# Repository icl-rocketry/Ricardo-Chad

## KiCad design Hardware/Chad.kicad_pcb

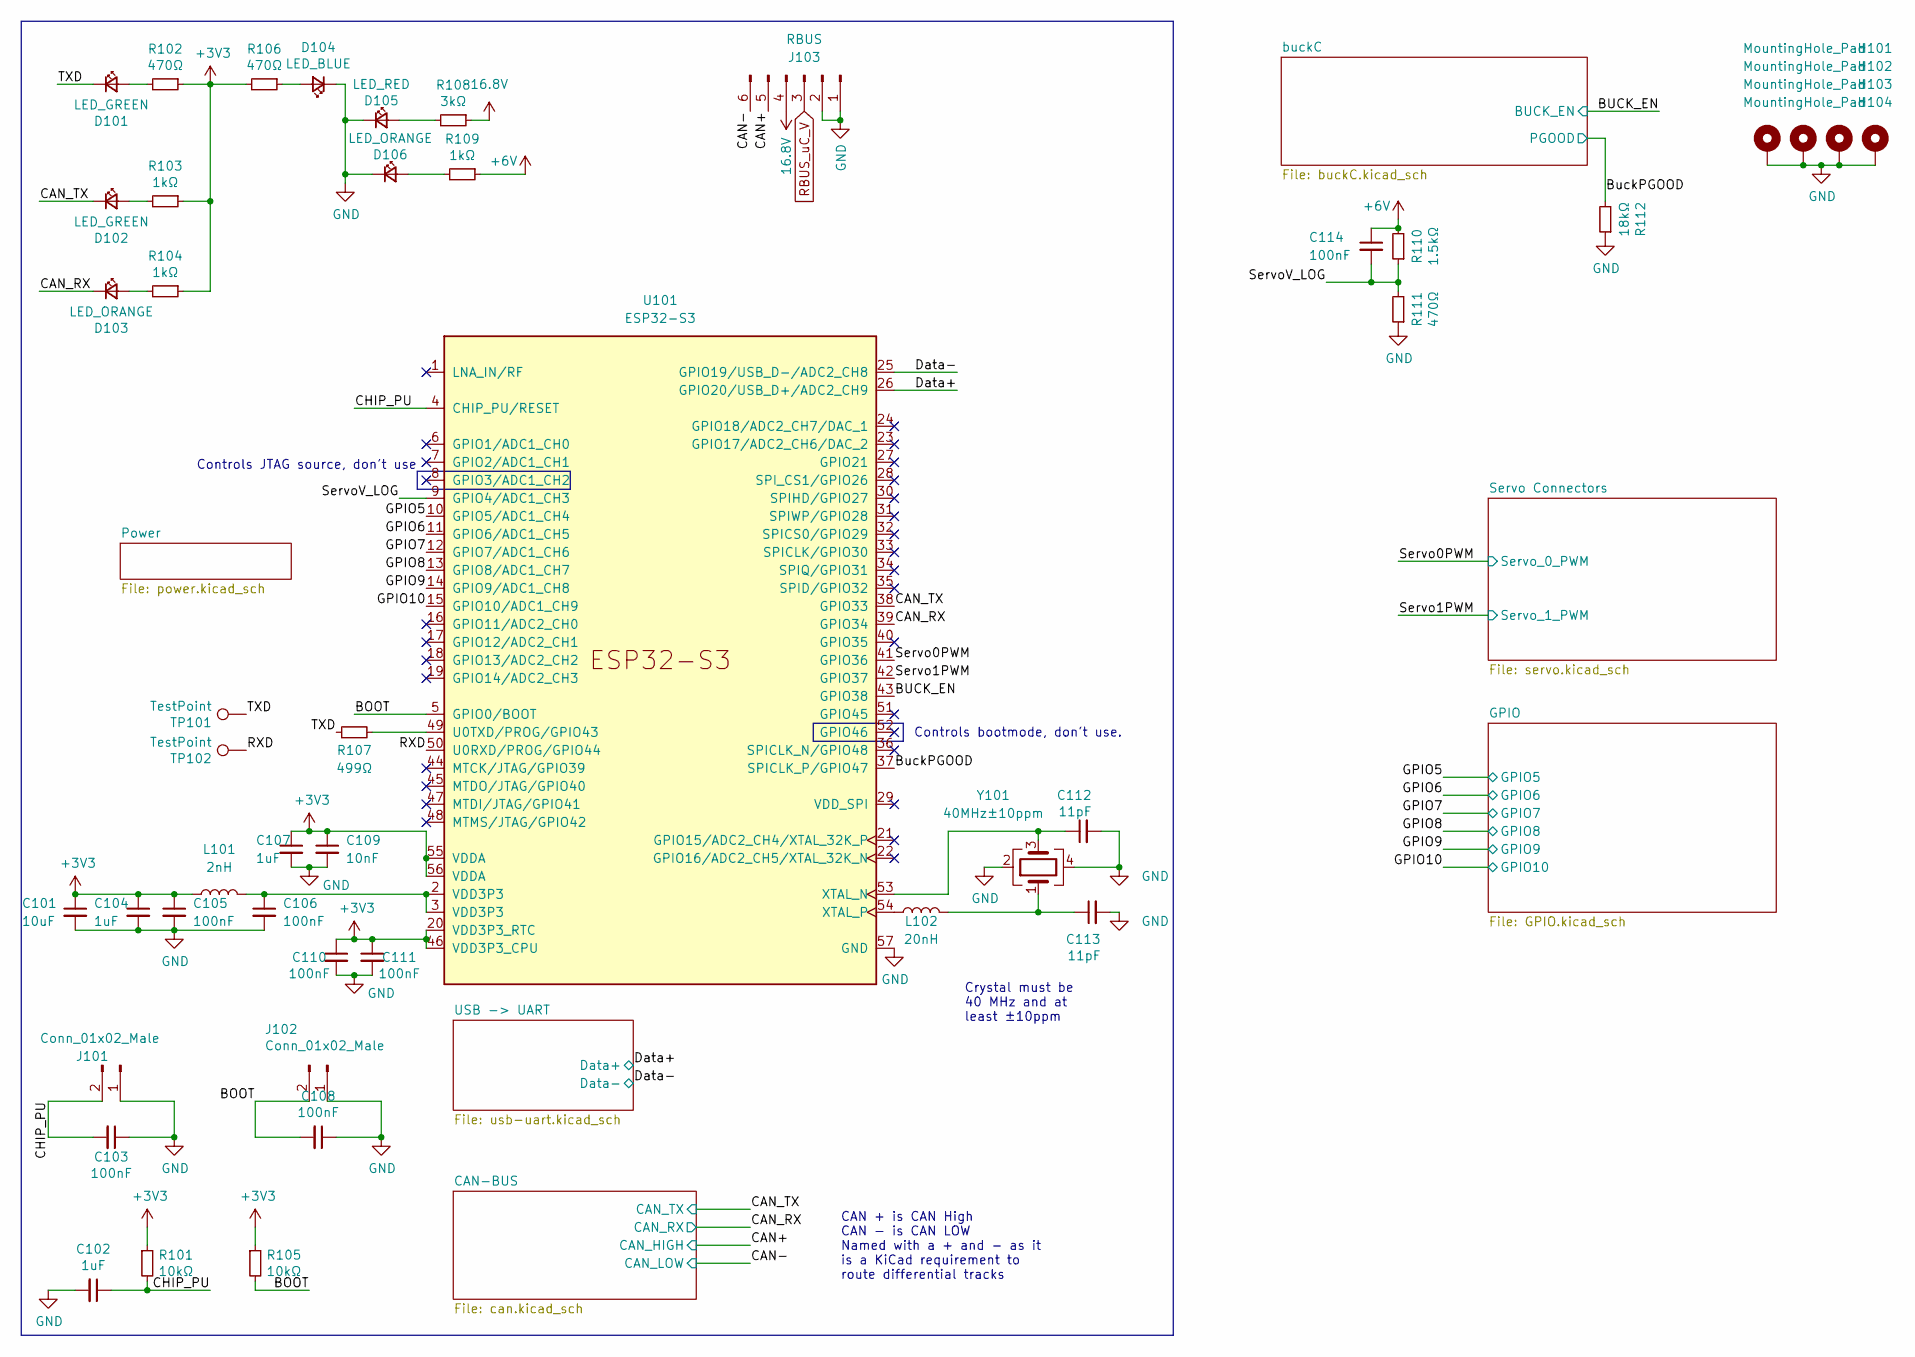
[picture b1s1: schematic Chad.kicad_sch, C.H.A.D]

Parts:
C101: 10uF; C_0402_1005Metric
C102, C104, C107: 1uF; C_0402_1005Metric
C103, C105, C106, C108, C110, C111, C114: 100nF; C_0402_1005Metric
C109: 10nF; C_0402_1005Metric
C112, C113: 11pF; C_0402_1005Metric
D101, D102: LED_GREEN; LED_0402_1005Metric
D103, D106: LED_ORANGE; LED_0402_1005Metric
D104: LED_BLUE; LED_0402_1005Metric
D105: LED_RED; LED_0402_1005Metric
H101, H102, H103, H104: MountingHole_Pad; MountingHole_3.2mm_M3_DIN965_Pad
J101, J102: Conn_01x02_Male; PinHeader_1x02_P2.54mm_Vertical
J103: RBUS; Molex_Mini-Fit_Jr_5569-06A2_2x03_P4.20mm_Horizontal
L101: 2nH; L_0402_1005Metric
L102: 20nH; L_0402_1005Metric
R101, R105: 10kΩ; R_0402_1005Metric
R102, R106, R111: 470Ω; R_0402_1005Metric
R103, R104, R109: 1kΩ; R_0402_1005Metric
R107: 499Ω; R_0402_1005Metric; MPN AC0402FR-07499RL
R108: 3kΩ; R_0402_1005Metric
R110: 1.5kΩ; R_0402_1005Metric
R112: 18kΩ; R_0402_1005Metric
TP101, TP102: TestPoint; TestPoint_Pad_D1.0mm
U101: ESP32-S3; QFN40P700X700X90-57N
Y101: 40MHz±10ppm; Crystal_SMD_2016-4Pin_2.0x1.6mm; MPN R940000171

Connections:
+3V3: C101.1, C104.1, C105.1, C107.1, C109.1, C110.1, C111.1, L101.1, R101.1, R102.1, R103.1, R104.1, R105.1, R106.2, U101.20 (VDD3P3_RTC), U101.46 (VDD3P3_CPU), U101.55 (VDDA), U101.56 (VDDA); also elsewhere on the board
+6V: C114.1, R109.1, R110.2; also elsewhere on the board
+16.8V: J103.4, R108.1; also elsewhere on the board
/BOOT: C108.2, J102.2, R105.2, U101.5 (GPIO0/BOOT)
/BUCK_EN: U101.43 (GPIO38); also elsewhere on the board
/BuckPGOOD: R112.2, U101.37 (SPICLK_P/GPIO47); also elsewhere on the board
/CAN+: J103.5; also elsewhere on the board
/CAN-: J103.6; also elsewhere on the board
/CAN_RX: D103.1 (K), U101.39 (GPIO34); also elsewhere on the board
/CAN_TX: D102.1 (K), U101.38 (GPIO33); also elsewhere on the board
/CHIP_PU: C102.1, C103.2, J101.2, R101.2, U101.4 (CHIP_PU/RESET)
/Data+: U101.26 (GPIO20/USB_D+/ADC2_CH9); also elsewhere on the board
/Data-: U101.25 (GPIO19/USB_D-/ADC2_CH8); also elsewhere on the board
/GPIO5: U101.10 (GPIO5/ADC1_CH4); also elsewhere on the board
/GPIO6: U101.11 (GPIO6/ADC1_CH5); also elsewhere on the board
/GPIO7: U101.12 (GPIO7/ADC1_CH6); also elsewhere on the board
/GPIO8: U101.13 (GPIO8/ADC1_CH7); also elsewhere on the board
/GPIO9: U101.14 (GPIO9/ADC1_CH8); also elsewhere on the board
/GPIO10: U101.15 (GPIO10/ADC1_CH9); also elsewhere on the board
/RXD: TP102.1, U101.50 (U0RXD/PROG/GPIO44)
/Servo0PWM: U101.41 (GPIO36); also elsewhere on the board
/Servo1PWM: U101.42 (GPIO37); also elsewhere on the board
/ServoV_LOG: C114.2, R110.1, R111.2, U101.9 (GPIO4/ADC1_CH3)
/TXD: D101.1 (K), R107.1, TP101.1
GND: C101.2, C102.2, C103.1, C104.2, C105.2, C106.2, C107.2, C108.1, C109.2, C110.2, C111.2, C112.2, C113.2, D104.1 (K), D105.1 (K), D106.1 (K), H101.1, H102.1, H103.1, H104.1, J101.1, J102.1, J103.1, J103.2, R111.1, R112.1, U101.57 (GND), Y101.2, Y101.4; also elsewhere on the board
unnamed: C106.1, L101.2, U101.2 (VDD3P3), U101.3 (VDD3P3)
unnamed: C113.1, L102.2, Y101.1
unnamed: D101.2 (A), R102.2
unnamed: D102.2 (A), R103.2
unnamed: D103.2 (A), R104.2
unnamed: D104.2 (A), R106.1
unnamed: D105.2 (A), R108.2
unnamed: D106.2 (A), R109.2
unnamed: R107.2, U101.49 (U0TXD/PROG/GPIO43)
unnamed: C112.1, U101.53 (XTAL_N), Y101.3
unnamed: L102.1, U101.54 (XTAL_P)
RBUS_uC_V: J103.3; also elsewhere on the board

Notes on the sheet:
Controls bootmode, don't use.
CAN + is CAN High CAN - is CAN LOW Named with a + and - as it is a KiCad requirement to route differential tracks
Controls JTAG source, don't use
Crystal must be 40 MHz and at least ±10ppm

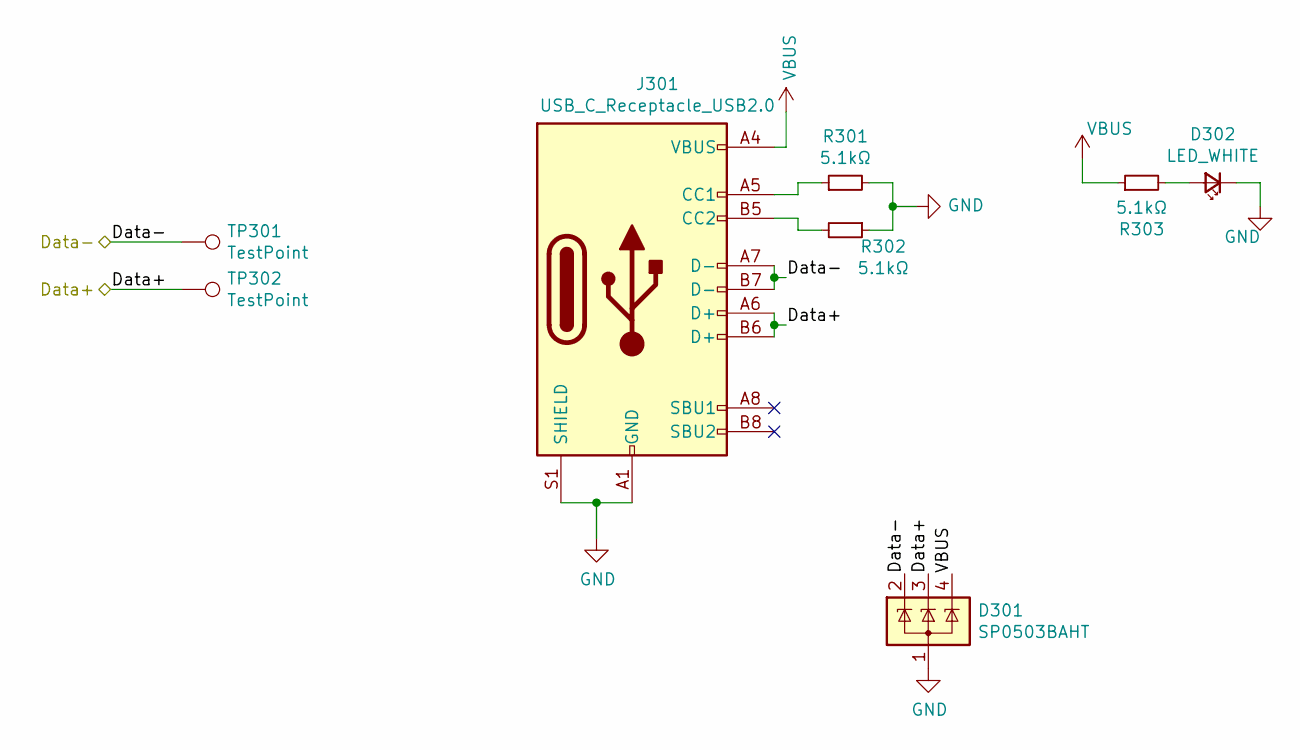
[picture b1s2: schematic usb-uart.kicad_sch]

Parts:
D301: SP0503BAHT; SOT-143
D302: LED_WHITE; LED_0402_1005Metric
J301: USB_C_Receptacle_USB2.0; USB_C_Receptacle_Palconn_UTC16-G
R301, R302, R303: 5.1kΩ; R_0402_1005Metric
TP301, TP302: TestPoint; TestPoint_Pad_D1.0mm

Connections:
/Data+: D301.3 (K), J301.A6 (D+), J301.B6 (D+), TP302.1; also elsewhere on the board
/Data-: D301.2 (K), J301.A7 (D-), J301.B7 (D-), TP301.1; also elsewhere on the board
GND: D301.1 (A), D302.1 (K), J301.A1 (GND), J301.A12 (GND), J301.B1 (GND), J301.B12 (GND), J301.S1 (SHIELD), R301.2, R302.1; also elsewhere on the board
unnamed: D302.2 (A), R303.2
unnamed: J301.A5 (CC1), R301.1
unnamed: J301.B5 (CC2), R302.2
VBUS: D301.4 (K), J301.A4 (VBUS), J301.A9 (VBUS), J301.B4 (VBUS), J301.B9 (VBUS), R303.1; also elsewhere on the board

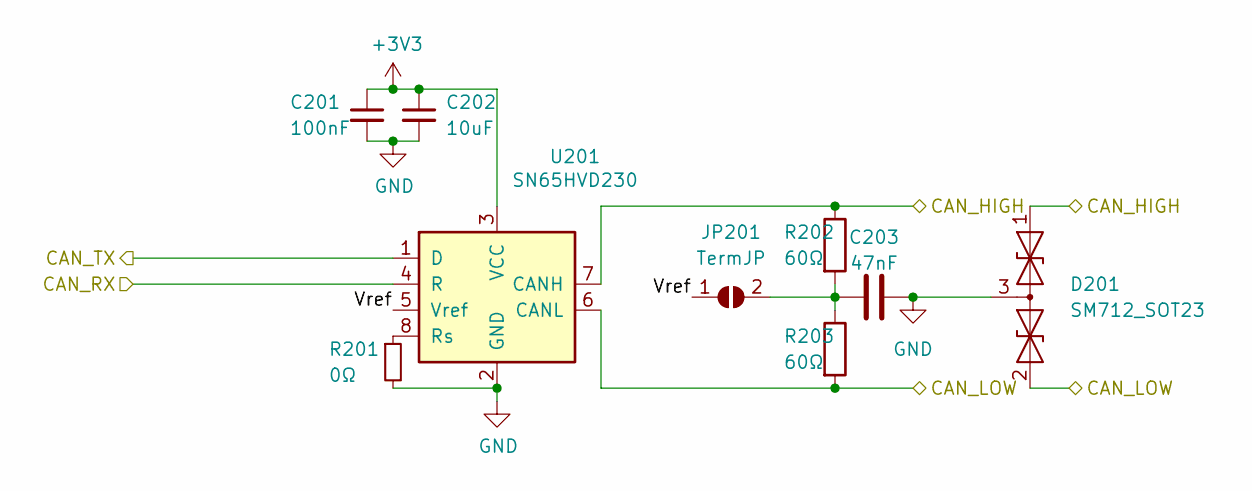
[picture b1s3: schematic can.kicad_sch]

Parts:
C201: 100nF; C_0402_1005Metric
C202: 10uF; C_0402_1005Metric
C203: 47nF; C_0402_1005Metric
D201: SM712_SOT23; SOT-23
JP201: TermJP; SmallerSolderJP
R201: 0Ω; R_0402_1005Metric
R202, R203: 60Ω; R_0603_1608Metric
U201: SN65HVD230; SOIC-8_3.9x4.9mm_P1.27mm

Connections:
+3V3: C201.1, C202.1, U201.3 (VCC); also elsewhere on the board
/CAN+: D201.1 (A1), R202.1, U201.7 (CANH); also elsewhere on the board
/CAN-: D201.2 (A2), R203.2, U201.6 (CANL); also elsewhere on the board
/CAN-BUS/Vref: JP201.1 (A), U201.5 (Vref)
/CAN_RX: U201.4 (R); also elsewhere on the board
/CAN_TX: U201.1 (D); also elsewhere on the board
GND: C201.2, C202.2, C203.2, D201.3 (common), R201.2, U201.2 (GND); also elsewhere on the board
unnamed: C203.1, JP201.2 (B), R202.2, R203.1
unnamed: R201.1, U201.8 (Rs)

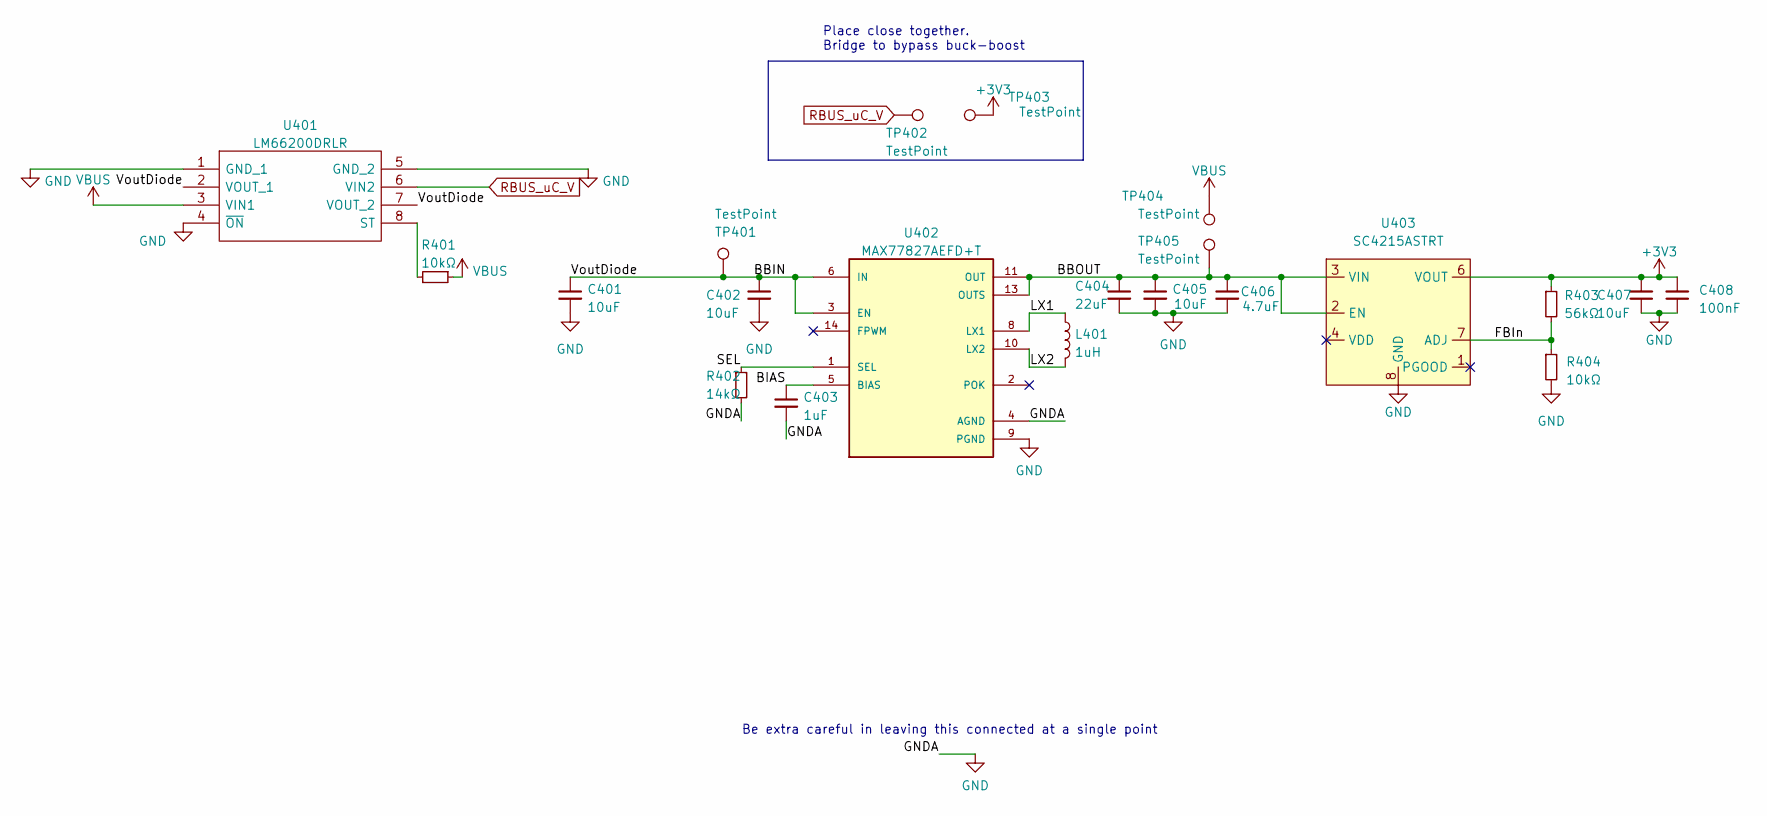
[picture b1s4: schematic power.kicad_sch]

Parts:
C401, C405, C407: 10uF; C_0402_1005Metric
C402: 10uF; C_0603_1608Metric
C403: 1uF; C_0402_1005Metric
C404: 22uF; C_0603_1608Metric
C406: 4.7uF; C_0402_1005Metric
C408: 100nF; C_0402_1005Metric
L401: 1uH; L_0805_2012Metric; MPN DFE201210U-1R0M
R401, R404: 10kΩ; R_0402_1005Metric
R402: 14kΩ; R_0402_1005Metric
R403: 56kΩ; R_0402_1005Metric
TP401, TP402, TP403, TP404, TP405: TestPoint; TestPoint_Pad_D1.5mm
U401: LM66200DRLR; SOTFL50P160X60-8N; Manufacturer_Part_Number LM66200DRLR; Mouser Part Number 595-LM66200DRLR
U402: MAX77827AEFD+T; CONV_MAX77827AEFD+T; PARTREV B
U403: SC4215ASTRT; SOIC127P599X175-9N

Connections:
+3V3: C407.2, C408.2, R403.1, TP403.1, U403.6 (VOUT); also elsewhere on the board
/Power/BBIN: C401.1, C402.1, TP401.1, U401.2 (VOUT_1), U401.7 (VOUT_2), U402.3 (EN), U402.6 (IN)
/Power/BBOUT: C404.1, C405.1, C406.1, TP405.1, U402.11 (OUT), U402.13 (OUTS), U403.2 (EN), U403.3 (VIN)
/Power/BIAS: C403.1, U402.5 (BIAS)
/Power/FBIn: R403.2, R404.1, U403.7 (ADJ)
/Power/LX1: L401.1, U402.8 (LX1)
/Power/LX2: L401.2, U402.10 (LX2)
/Power/SEL: R402.1, U402.1 (SEL)
GND: C401.2, C402.2, C403.2, C404.2, C405.2, C406.2, C407.1, C408.1, R402.2, R404.2, U401.1 (GND_1), U401.4 (~ON), U401.5 (GND_2), U402.4 (AGND), U402.9 (PGND), U403.8 (GND), U403.9 (GND); also elsewhere on the board
unnamed: R401.2, U401.8 (ST)
RBUS_uC_V: TP402.1, U401.6 (VIN2); also elsewhere on the board
VBUS: R401.1, TP404.1, U401.3 (VIN1); also elsewhere on the board

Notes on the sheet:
Place close together. Bridge to bypass buck-boost
Be extra careful in leaving this connected at a single point

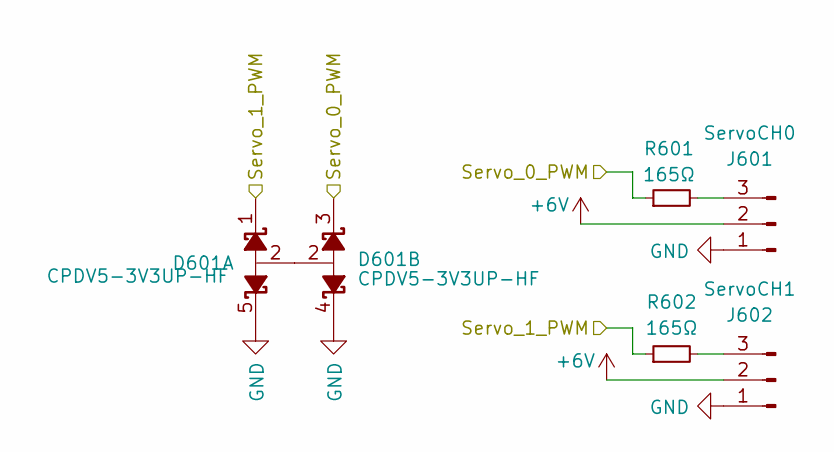
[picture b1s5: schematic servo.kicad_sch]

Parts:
D601: CPDV5-3V3UP-HF; SOT-353_SC-70-5
J601: ServoCH0; Molex_Nano-Fit_105313-xx03_1x03_P2.50mm_Horizontal
J602: ServoCH1; Molex_Nano-Fit_105313-xx03_1x03_P2.50mm_Horizontal
R601, R602: 165Ω; R_0402_1005Metric; MPN RK73H1ETTP1650F

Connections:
+6V: J601.2, J602.2; also elsewhere on the board
/Servo0PWM: D601.3, R601.1; also elsewhere on the board
/Servo1PWM: D601.1, R602.1; also elsewhere on the board
GND: D601.4, D601.5, J601.1, J602.1; also elsewhere on the board
unnamed: J601.3, R601.2
unnamed: J602.3, R602.2

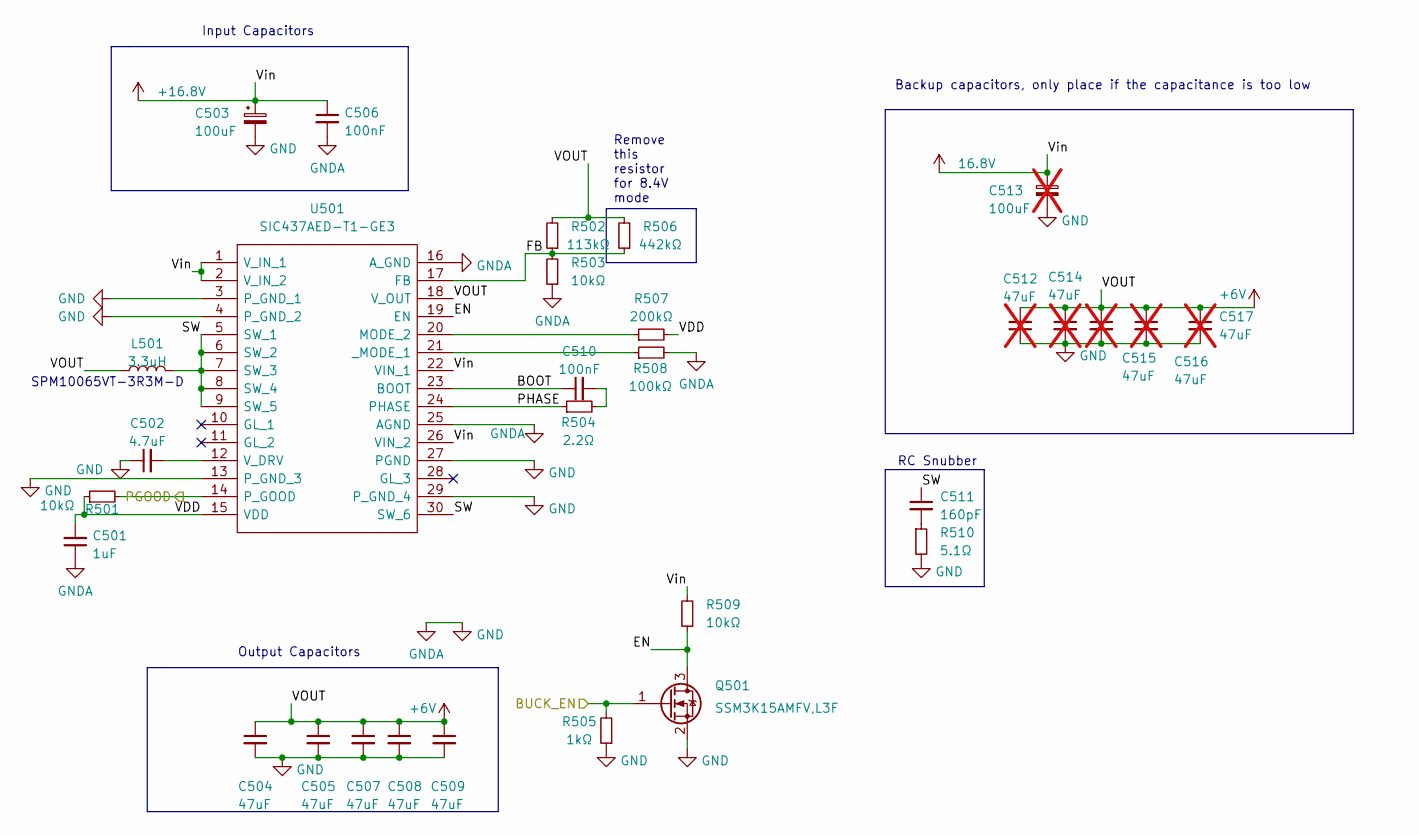
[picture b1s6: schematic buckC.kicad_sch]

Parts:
C501: 1uF; C_0402_1005Metric
C502: 4.7uF; C_0402_1005Metric
C503: 100uF; CP_EIA-7360-38_Kemet-E; MPN T52M1107M035C0100
C504, C505, C507, C508, C509: 47uF; C_1206_3216Metric
C506, C510: 100nF; C_0402_1005Metric
C511: 160pF; C_0603_1608Metric
C512, C514, C515, C516, C517: 47uF; C_1206_3216Metric; not fitted
C513: 100uF; CP_EIA-7360-38_Kemet-E; MPN T52M1107M035C0100; not fitted
L501: 3.3uH; IND_SPM10065VT-3R3M-D; MPN SPM10065VT-3R3M-D
Q501: SSM3K15AMFV,L3F; SOT-723
R501, R503, R509: 10kΩ; R_0402_1005Metric
R502: 113kΩ; R_0402_1005Metric; MPN ERJ-2RKF1133X
R504: 2.2Ω; R_0402_1005Metric
R505: 1kΩ; R_0402_1005Metric
R506: 442kΩ; R_0402_1005Metric; MPN ERJ-2RKF4423X
R507: 200kΩ; R_0402_1005Metric
R508: 100kΩ; R_0402_1005Metric
R510: 5.1Ω; R_0603_1608Metric
U501: SIC437AED-T1-GE3; SiC437BEDT1GE3; Manufacturer_Part_Number SiC437BED-T1-GE3; Mouser Part Number 78-SIC437BED-T1-GE3

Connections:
+6V: C504.1, C505.1, C507.1, C508.1, C509.1, C512.2, C514.1, C515.1, C516.1, C517.1, L501.1, R502.2, R506.2, U501.18 (V_OUT); also elsewhere on the board
+16.8V: C503.1, C506.1, C513.1, R509.2, U501.1 (V_IN_1), U501.2 (V_IN_2), U501.22 (VIN_1), U501.26 (VIN_2); also elsewhere on the board
/BUCK_EN: Q501.1 (G), R505.2; also elsewhere on the board
/BuckPGOOD: R501.2, U501.14 (P_GOOD); also elsewhere on the board
/buckC/BOOT: C510.1, U501.23 (BOOT)
/buckC/EN: Q501.3 (D), R509.1, U501.19 (EN)
/buckC/FB: R502.1, R503.2, R506.1, U501.17 (FB)
/buckC/PHASE: R504.1, U501.24 (PHASE)
/buckC/SW: C511.1, L501.2, U501.5 (SW_1), U501.6 (SW_2), U501.7 (SW_3), U501.8 (SW_4), U501.9 (SW_5), U501.30 (SW_6)
/buckC/VDD: C501.2, R501.1, R507.2, U501.15 (VDD)
GND: C501.1, C502.1, C503.2, C504.2, C505.2, C506.2, C507.2, C508.2, C509.2, C512.1, C513.2, C514.2, C515.2, C516.2, C517.2, Q501.2 (S), R503.1, R505.1, R508.2, R510.2, U501.3 (P_GND_1), U501.4 (P_GND_2), U501.13 (P_GND_3), U501.16 (A_GND), U501.25 (AGND), U501.27 (PGND), U501.29 (P_GND_4); also elsewhere on the board
unnamed: C510.2, R504.2
unnamed: C511.2, R510.1
unnamed: R507.1, U501.20 (MODE_2)
unnamed: C502.2, U501.12 (V_DRV)
unnamed: R508.1, U501.21 (_MODE_1)

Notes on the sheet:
Backup capacitors, only place if the capacitance is too low
RC Snubber
SPM10065VT-3R3M-D
Input Capacitors
Output Capacitors
Remove this resistor for 8.4V mode

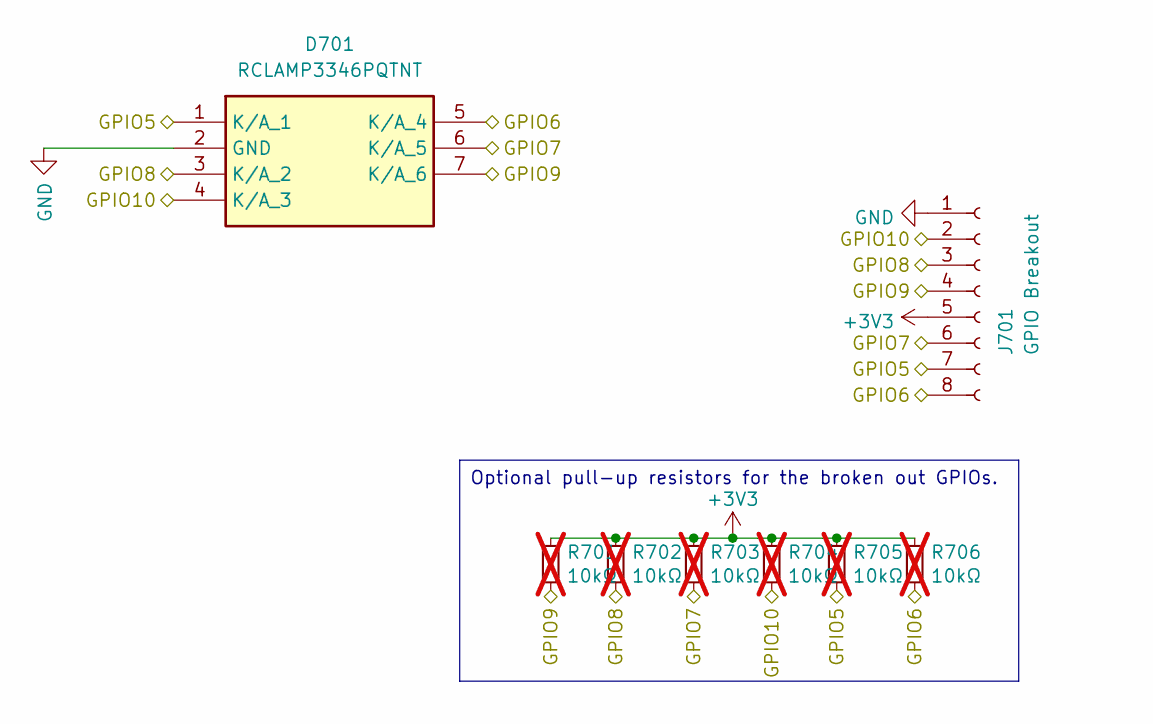
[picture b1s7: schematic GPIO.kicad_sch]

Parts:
D701: RCLAMP3346PQTNT; Mouser Part Number 947-RCLAMP3346PQTNT
J701: GPIO Breakout; PinSocket_2x04_P2.54mm_Vertical
R701, R702, R703, R704, R705, R706: 10kΩ; R_0402_1005Metric; not fitted

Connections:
+3V3: J701.5, R701.1, R702.1, R703.1, R704.1, R705.1, R706.1; also elsewhere on the board
/GPIO5: D701.1 (K/A_1), J701.7, R705.2; also elsewhere on the board
/GPIO6: D701.5 (K/A_4), J701.8, R706.2; also elsewhere on the board
/GPIO7: D701.6 (K/A_5), J701.6, R703.2; also elsewhere on the board
/GPIO8: D701.3 (K/A_2), J701.3, R702.2; also elsewhere on the board
/GPIO9: D701.7 (K/A_6), J701.4, R701.2; also elsewhere on the board
/GPIO10: D701.4 (K/A_3), J701.2, R704.2; also elsewhere on the board
GND: D701.2 (GND), J701.1; also elsewhere on the board

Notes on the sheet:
Optional pull-up resistors for the broken out GPIOs.

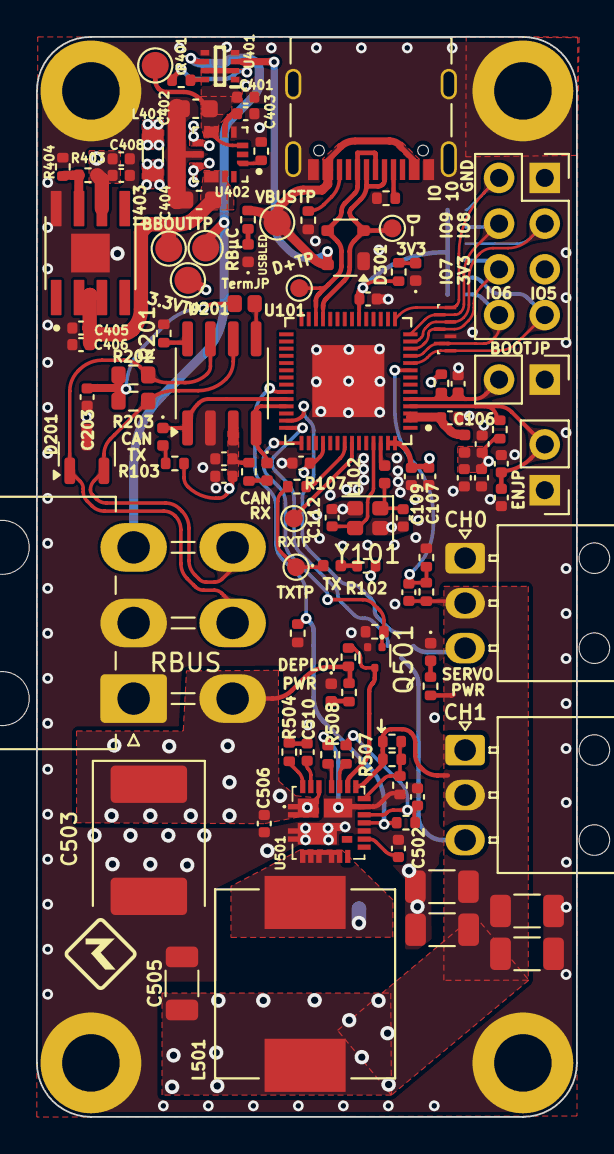
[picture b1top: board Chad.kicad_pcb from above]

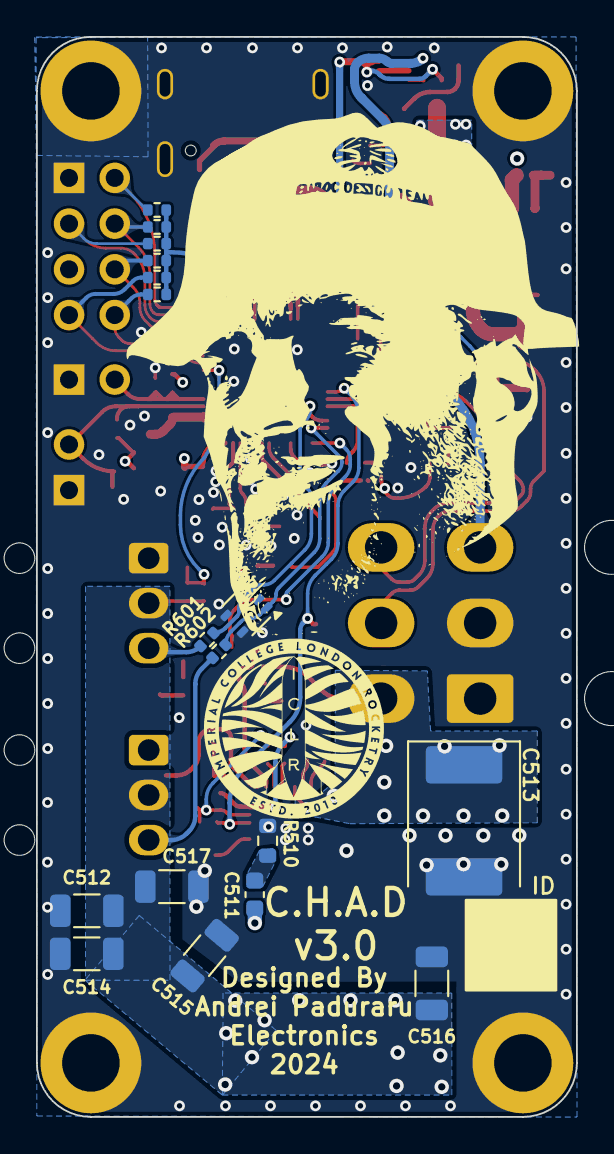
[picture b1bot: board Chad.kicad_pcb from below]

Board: 4 copper layers, 30.0 x 60.0 mm, 127 parts (18 on the bottom side), 65 nets.

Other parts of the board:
LOGO1: ICLR LOGO; iclr_logo_estd2018_10mm

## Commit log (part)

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2024-02-11 added simple engine controller
2024-02-12 Thanos-R hotfire 11/02/2024 fixes
2024-02-13 Added tvc controller and debug stuff
2024-02-14 fixed pins being setup as inputs and random command switching
2024-02-16 O drive state machine
2024-02-19 TVC armed state
2024-02-19 updated librrc
2024-02-19 Forgot to call odrive state machine ...
2024-02-19 Updating Librrc Submodules
2024-02-19 Updated pinmap for gss
2024-02-20 chamberP based throttling
2024-02-20 added csv with controller params
2024-02-23 changed calls to motor functions to oDriveState changes
2024-02-23 ox fill open during test
2024-02-23 limited to 2 sends of closeoxfill
2024-02-24 cold flow setup
2024-02-24 kiran fixes
2024-02-24 kiran arming fix
2024-02-24 and again
2024-02-25 Sunday regen hotfire
2024-02-25 1st tvc hotfire of the day
2024-02-29 Added license
2024-03-06 overrdie servo callibration and change counts range
2024-03-06 modification for tvc demo
2024-03-07 updated arduino
2024-03-08 not sure why i had to do this
2024-03-23 glow plug controller
2024-06-04 Updated Chad For Propellor
2024-06-04 wip GNC states
2024-06-08 wip states on chad for prop
    created files and made basic pseudocode
2024-06-10 flight hardware test
2024-06-10 fixed errors
2024-06-13 Updated engine controller
2024-06-15 WIP updated GNC state and class info
    changed GNCstate to GNC, updated states so it changes between them, created classes in GNC, added an external and internal servo. we still have errors :)
2024-06-18 WIP fixing a ton of include files
    fixed most errors in the GNC folder, 1 more to go. most of it was include stuff
2024-06-22 forgot to push with the others on tuesday
2024-07-07 checking states and nrcprop
2024-07-08 removed thanos controller
2024-07-08 submodule commits
2024-07-08 Pulled in voltage reading fix from other branches
2024-07-08 .DS_Store cleanup
2024-07-08 changed project name in cmake
2024-07-11 Maybe chad v3.0 hardware
2024-07-11 RAE logo
2024-07-12 Buck converter error flag
2024-08-15 30V compatibility update
2024-08-17 Resistor values
2024-08-18 Added GPIO TVS protection
2024-08-22 Fixed buck class spams serial bug
2024-08-28 fixed minor pinmap issue
2024-09-04 updated to new servo class
2024-09-05 split buck error into 2 different flags
2024-09-05 fixed pgood hardware issue
2024-09-05 submodule commit
2024-09-07 Fixed both servos running on same local PWM
2024-09-10 v3 ordered
2024-09-27 some renaming and submodules
2024-09-28 switched to 240MHz
2024-10-21 moving to main branches of submodules
2024-10-21 v3.0 release
2024-10-21 fixed wrong submodule commit
2024-11-26 push to hand off to arlo
2024-11-29 Watchdog Timer added
2024-12-03 Basic commands setup
2024-12-07 GNC files moved
2024-12-07 Rename files and move to single file
2024-12-10 Created more generic interface
2024-12-10 Changed class def in packet
2024-12-11 Testing fixes
2024-12-13 Added higher level network interface for TVC
2024-12-13 Not sure what happened here, does not move
2024-12-14 Hotfire almost fixes
2024-12-14 Fixes for hotfire (integer division)
2024-12-14 EOD Hotfire
2024-12-15 Added vel and pos gain
2025-01-09 .ini changes and submodule updates, removed vrailmonitor momentarily as old ADC api doesn't compile
2025-01-09 ignore managed_components...
2025-02-01 API Change in librrc means LocalPWM constructor is used differentlygit statusgit statusgit status
2025-02-01 Copied Kiran's vrail monitor for servo voltage, this should eventually be a HAL...
2025-02-13 Some small fixes for new actuators
2025-02-15 Added Watchdog Files
2025-02-15 Added nrcpropfiles from moveover
    ya tbh this probably isnt working atm
2025-02-15 Started defining new TVC interface
2025-02-15 WatchdogWork
    not working yet, close - created PID network manager
2025-02-18 feat: Good progress over new TVC interface and statful controller
2025-02-18 fix: Fixed compilation errors and removed old interface
2025-02-18 feat: Starting error handling and printing
2025-02-18 more watchdog updates
    config updated
2025-02-18 added GNC props, WatchDog testable
2025-02-18 feat: Add some hacky things for testing
2025-02-18 feat: More fixes
2025-02-19 Started TVC commands, motor works
2025-02-19 feat: Updated file names.
2025-02-19 feat: Started state
2025-02-21 feat: Some work on states
2025-02-21 feat: test program for integration
2025-02-21 fix: Setting running state
2025-02-21 none
2025-02-22 feat: Good progress on TVC state handling
2025-02-22 feat: Added programs
2025-02-25 Almost* Got WatchDog working
2025-02-25 WatchDog working - timeout 2 seconds
    Dirty Code, clean push will happen soon
2025-03-07 Updated menuconfig to new template conf + submodules to v4-DEV
2025-03-15 feat: Updates to clean up interface
2025-03-15 feat: Remove types
2025-03-22 fix: Fixed import name
2025-08-13 push before i forget, rtk close to working but doesnt
2025-09-10 feat: Chad FTS software implemented
2025-10-11 fix: Change commandTimeoutMS
2025-10-12 feat: Finalising FTS Firmware
2025-10-12 fix: FTS reading High
2025-12-27 v4 submodule tags
2026-03-07 Initial Branch commit
2026-03-07 Inital commit
2026-03-07 Working Update
2026-03-07 OLED testing update
2026-03-27 no idea what this is lmao
2026-03-27 updated hole size for eurocircuits
2026-04-07 inshallah i dont push this to remote
2026-05-12 Working Display
2026-05-16 Low-pass filter working
2026-05-29 Implement GNC throttle changes
2026-06-06 RTK seems to be working, now testing integration
2026-06-07 Added better serial print debugging
2026-06-12 RTK working, revert to here if nothing else is working
2026-06-13 RTK time stamping, ntrip client is now on external esp32
2026-06-22 Servo angles updated
2026-06-24 cleaned up schematic and bom
2026-06-24 continued
